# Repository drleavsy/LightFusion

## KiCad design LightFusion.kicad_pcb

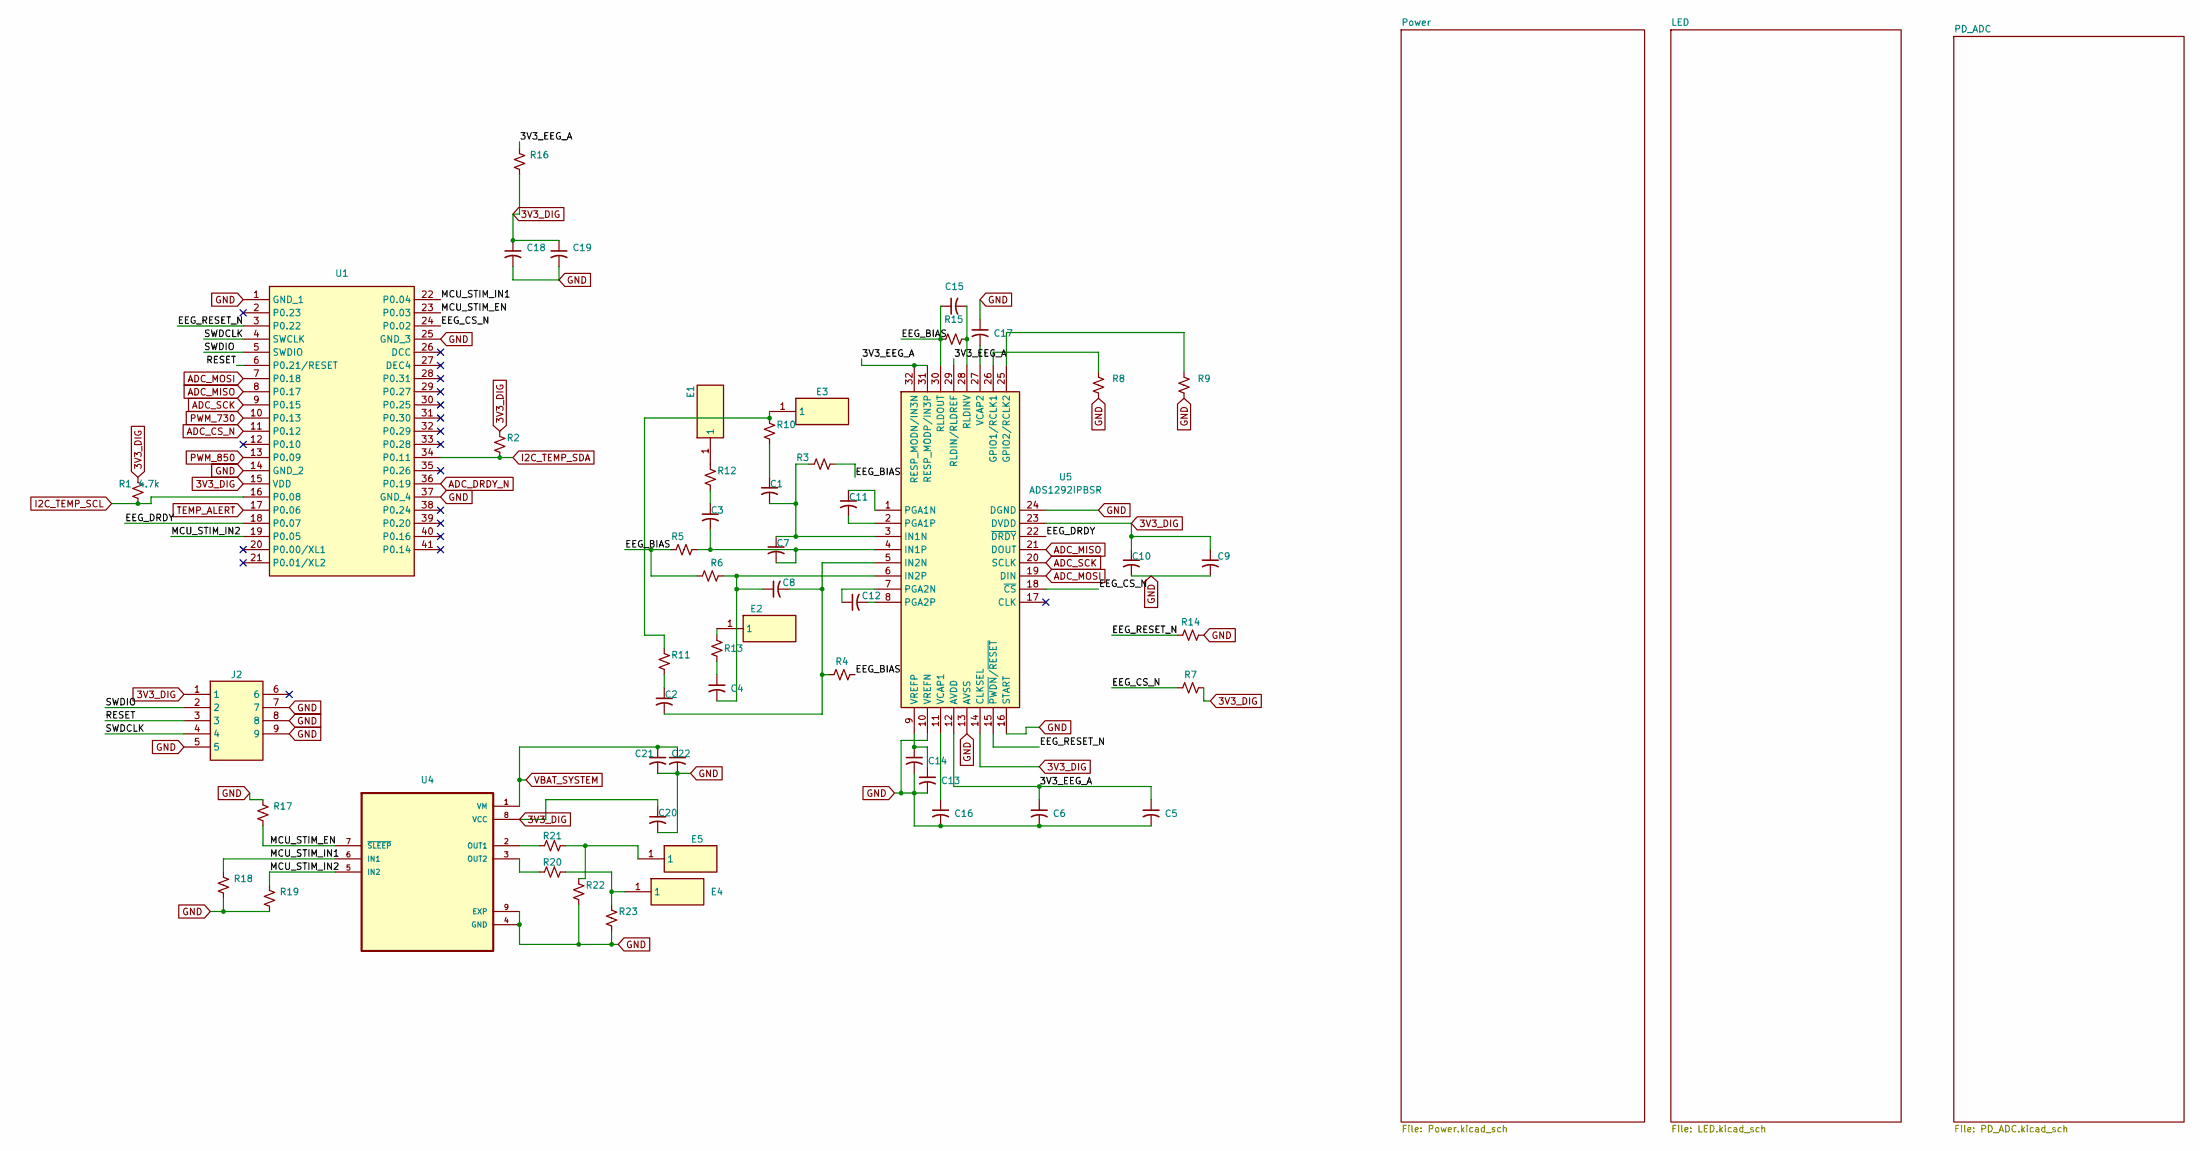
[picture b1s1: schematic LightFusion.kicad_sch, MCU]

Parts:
C1, C2, C3, C4: 47 nF; C_1206_3216Metric
C5, C9, C13: 10 µF; C_0603_1608Metric
C6, C10, C14, C18, C20, C21: 100 nF; C_0603_1608Metric
C7, C8: 2.2 nF; C_0402_1005Metric
C11, C12: 4.7 nF; C_0402_1005Metric
C15: 1.5 nF; C_0402_1005Metric
C16, C17: 1 µF; CAPPC2012X90N
C19: 4.7 uF; C_0603_1608Metric
C22: 1 µF; C_0603_1608Metric
E1, E2, E3, E4, E5: 0914015207714110; Mouser Part Number 575-914015
J2: TC2030-IDC-FP; TC2030IDCFP; Manufacturer_Part_Number TC2030-IDC-NL
R1, R2: 4.7k; R_0603_1608Metric
R3, R4, R5, R6: 22 MΩ; R_0603_1608Metric
R7, R14, R17, R18, R19: 100 kΩ; R_0603_1608Metric
R8, R9: 10 kΩ; R_0603_1608Metric
R10, R11, R12, R13: 51 kΩ; R_0603_1608Metric
R15, R22, R23: 1 MΩ; R_0603_1608Metric
R16: 10 Ω; R_0603_1608Metric
R20, R21: 22 kΩ; R_0603_1608Metric
U1: MDBT42-512KV2; MDBT42512KV2; PARTREV J
U4: DRV8837DSGR
U5: ADS1292IPBSR; Manufacturer_Part_Number ADS1292IPBSR; Mouser Part Number 595-ADS1292IPBSR

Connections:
3V3_DIG: C9.1, C10.1, C18.1, C19.1, C20.1, J2.1, R1.1, R2.1, R7.2, R16.2, U1.15 (VDD), U4.8 (VCC), U5.14 (CLKSEL), U5.23 (DVDD); also elsewhere on the board
/3V3_EEG_A: C5.1, C6.1, R16.1, U5.12 (AVDD), U5.29 (RLDIN/RLDREF), U5.31 (RESP_MODP/IN3P), U5.32 (RESP_MODN/IN3N)
/EEG_BIAS: C15.1, R3.1, R4.2, R5.2, R6.2, R15.1, U5.30 (RLDOUT)
/EEG_CS_N: R7.1, U1.24 (P0.02), U5.18 (~CS)
/EEG_DRDY: U1.18 (P0.07), U5.22 (~DRDY)
/EEG_RESET_N: R14.1, U1.3 (P0.22), U5.15 (~PWDN/~RESET)
/MCU_STIM_EN: R17.2, U1.23 (P0.03), U4.7 (~SLEEP)
/MCU_STIM_IN1: R18.1, U1.22 (P0.04), U4.6 (IN1)
/MCU_STIM_IN2: R19.1, U1.19 (P0.05), U4.5 (IN2)
/RESET: J2.3, U1.6 (P0.21/RESET)
/SWDCLK: J2.4, U1.4 (SWCLK)
/SWDIO: J2.2, U1.5 (SWDIO)
ADC_CS_N: U1.11 (P0.12); also elsewhere on the board
ADC_DRDY_N: U1.36 (P0.19); also elsewhere on the board
ADC_MISO: U1.8 (P0.17), U5.21 (DOUT); also elsewhere on the board
ADC_MOSI: U1.7 (P0.18), U5.19 (DIN); also elsewhere on the board
ADC_SCK: U1.9 (P0.15), U5.20 (SCLK); also elsewhere on the board
GND: C5.2, C6.2, C9.2, C10.2, C13.2, C14.2, C16.2, C17.1, C18.2, C19.2, C20.2, C21.2, C22.2, J2.5, J2.7, J2.8, J2.9, R8.2, R9.2, R14.2, R17.1, R18.2, R19.2, R22.2, R23.2, U1.1 (GND_1), U1.14 (GND_2), U1.25 (GND_3), U1.37 (GND_4), U4.4 (GND), U4.9 (EXP), U5.10 (VREFN), U5.13 (AVSS), U5.16 (START), U5.24 (DGND); also elsewhere on the board
I2C_TEMP_SCL: R1.2, U1.16 (P0.08); also elsewhere on the board
I2C_TEMP_SDA: R2.2, U1.34 (P0.11); also elsewhere on the board
unnamed: C1.1, R10.2
unnamed: C2.1, R11.2
unnamed: C3.1, R12.2
unnamed: C4.1, R13.2
unnamed: E1.1 (1_1), R12.1
unnamed: E2.1 (1_1), R13.1
unnamed: E3.1 (1_1), R10.1, R11.1
unnamed: E4.1 (1_1), R20.2, R23.1
unnamed: E5.1 (1_1), R21.2, R22.1
unnamed: R21.1, U4.2 (OUT1)
unnamed: R20.1, U4.3 (OUT2)
unnamed: R8.1, U5.26 (GPIO1/RCLK1)
unnamed: R9.1, U5.25 (GPIO2/RCLK2)
unnamed: C1.2, C7.1, R3.2, U5.3 (IN1N)
unnamed: C3.2, C7.2, R5.1, U5.4 (IN1P)
unnamed: C2.2, C8.2, R4.1, U5.5 (IN2N)
unnamed: C4.2, C8.1, R6.1, U5.6 (IN2P)
unnamed: C11.1, U5.1 (PGA1N)
unnamed: C11.2, U5.2 (PGA1P)
unnamed: C12.1, U5.7 (PGA2N)
unnamed: C12.2, U5.8 (PGA2P)
unnamed: C15.2, R15.2, U5.28 (RLDINV)
unnamed: C16.1, U5.11 (VCAP1)
unnamed: C17.2, U5.27 (VCAP2)
unnamed: C13.1, C14.1, U5.9 (VREFP)
PWM_730: U1.10 (P0.13); also elsewhere on the board
PWM_850: U1.13 (P0.09); also elsewhere on the board
TEMP_ALERT: U1.17 (P0.06); also elsewhere on the board
VBAT_SYSTEM: C21.1, C22.1, U4.1 (VM); also elsewhere on the board

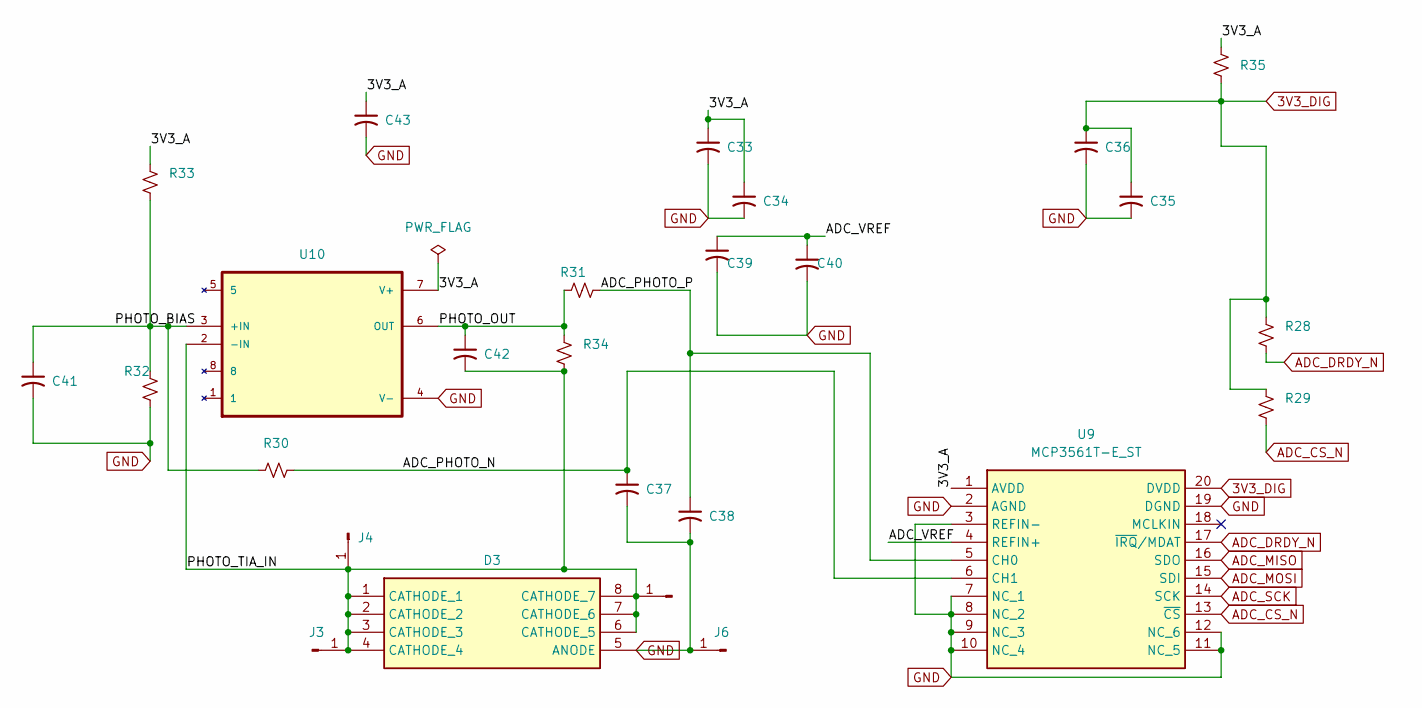
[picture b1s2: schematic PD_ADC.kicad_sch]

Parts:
C33, C34, C36, C40: 100 nF; C_0603_1608Metric
C35: 1uF; C_0603_1608Metric
C37, C38: 100nF; C_1206_3216Metric
C39, C41: 10uF; C_0603_1608Metric
C42: 6.8pF; C_0603_1608Metric
C43: 1 µF; C_0603_1608Metric
D3: VEMD8082; VEMD8082C; Manufacturer_Part_Number VEMD8082; Mouser Part Number 78-VEMD8082
J3, J4, J5, J6: Conn_01x01_Pin; TestPoint_THTPad_1.5x1.5mm_Drill0.7mm
R28, R29, R33, R34: 10k; R_0603_1608Metric
R30, R31: 100R; R_0603_1608Metric
R32: 1.8k; R_0603_1608Metric
R35: 10R; R_0603_1608Metric
U9: MCP3561T-E_ST; Manufacturer_Part_Number MCP3561T-E/ST; Mouser Part Number 579-MCP3561T-E/ST
U10: OPA381AIDGKR

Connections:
3V3_DIG: C35.1, C36.1, R28.1, R29.1, R35.1, U9.20 (DVDD); also elsewhere on the board
/PD_ADC/3V3_A: C33.1, C34.1, C43.1, R33.1, R35.2, U9.1 (AVDD), U10.7 (V+)
/PD_ADC/ADC_PHOTO_N: C37.1, R30.2, U9.6 (CH1)
/PD_ADC/ADC_PHOTO_P: C38.1, R31.2, U9.5 (CH0)
/PD_ADC/ADC_VREF: C39.1, C40.1, U9.4 (REFIN+)
/PD_ADC/PHOTO_BIAS: C41.1, R30.1, R32.1, R33.2, U10.3 (+IN)
/PD_ADC/PHOTO_OUT: C42.1, R31.1, R34.1, U10.6 (OUT)
/PD_ADC/PHOTO_TIA_IN: C42.2, D3.1 (CATHODE_1), D3.2 (CATHODE_2), D3.3 (CATHODE_3), D3.4 (CATHODE_4), D3.6 (CATHODE_5), D3.7 (CATHODE_6), D3.8 (CATHODE_7), J3.1 (Pin_1_1), J4.1 (Pin_1_1), J5.1 (Pin_1_1), R34.2, U10.2 (-IN)
ADC_CS_N: R29.2, U9.13 (~CS); also elsewhere on the board
ADC_DRDY_N: R28.2, U9.17 (~IRQ/MDAT); also elsewhere on the board
ADC_MISO: U9.16 (SDO); also elsewhere on the board
ADC_MOSI: U9.15 (SDI); also elsewhere on the board
ADC_SCK: U9.14 (SCK); also elsewhere on the board
GND: C33.2, C34.2, C35.2, C36.2, C37.2, C38.2, C39.2, C40.2, C41.2, C43.2, D3.5 (ANODE), J6.1 (Pin_1_1), R32.2, U9.2 (AGND), U9.3 (REFIN-), U9.7 (NC_1), U9.8 (NC_2), U9.9 (NC_3), U9.10 (NC_4), U9.11 (NC_5), U9.12 (NC_6), U9.19 (DGND), U10.4 (V-); also elsewhere on the board

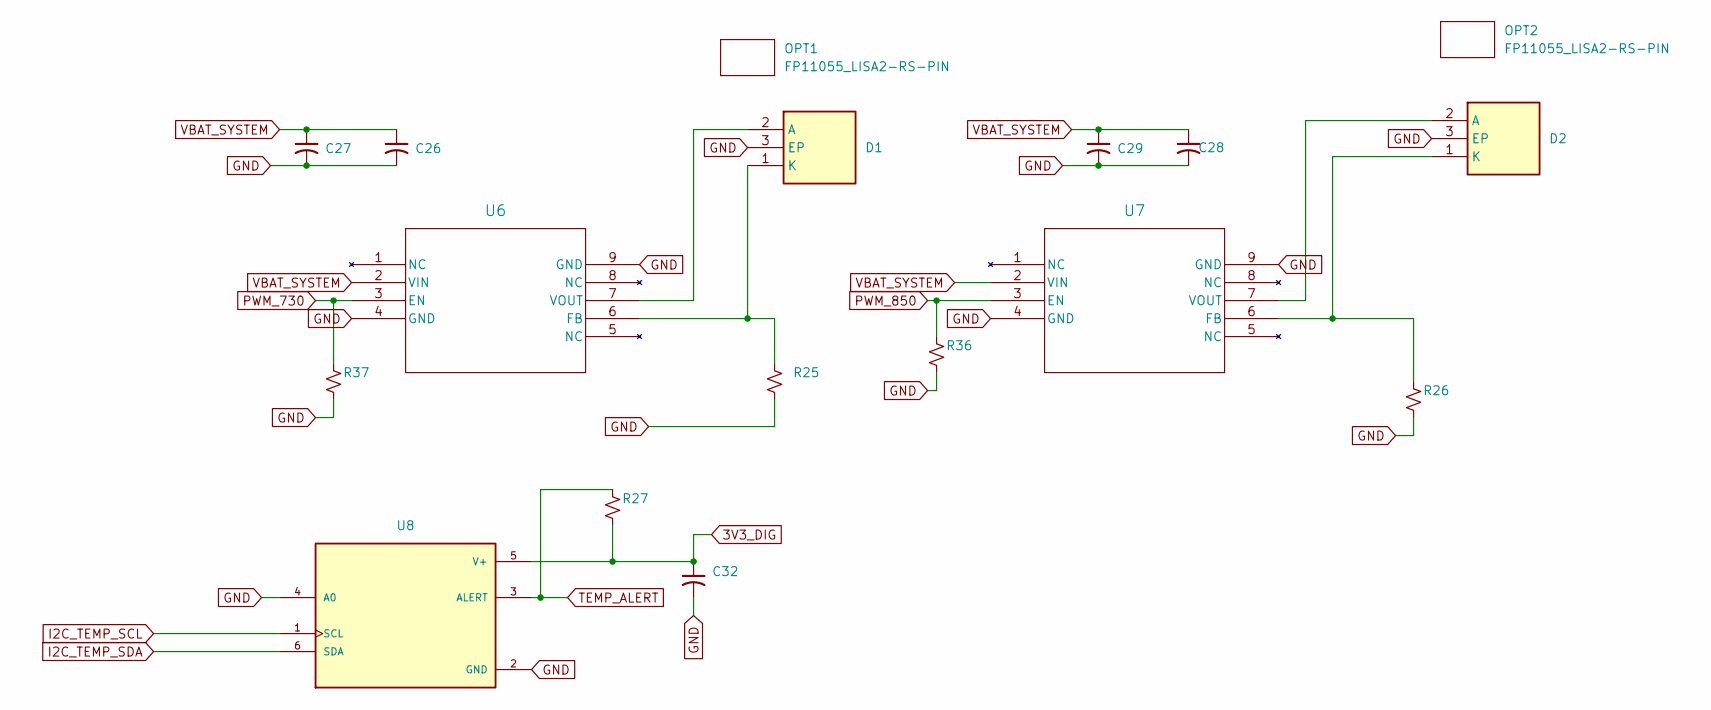
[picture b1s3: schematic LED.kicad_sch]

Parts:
C26, C28: 10 uF; C_0603_1608Metric
C27, C29: 100 nF; C_0603_1608Metric
C32: 10 nF; C_0603_1608Metric
D1, D2: SST-10-IRD-B90H-S810; SST10IRDB90HS810; Manufacturer_Part_Number SST-10-IRD-B90H-S810; Mouser Part Number 896-SST10IRDB90HS81
OPT1, OPT2: FP11055_LISA2-RS-PIN; LEDIL_FP11055_LISA2_RS_PIN
R25, R26: 0.13 Ohm; R_1206_3216Metric
R27: 4.7 kOhm; R_0603_1608Metric
R36, R37: 100k; R_0603_1608Metric
U6, U7: PAM2808BLBR
U8: TMP1075NDRLR; PARTREV E

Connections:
3V3_DIG: C32.1, R27.2, U8.5 (V+); also elsewhere on the board
GND: C26.2, C27.2, C28.2, C29.2, C32.2, D1.3 (EP), D2.3 (EP), R25.2, R26.2, R36.2, R37.2, U6.4 (GND), U6.9 (GND), U7.4 (GND), U7.9 (GND), U8.2 (GND), U8.4 (A0); also elsewhere on the board
I2C_TEMP_SCL: U8.1 (SCL); also elsewhere on the board
I2C_TEMP_SDA: U8.6 (SDA); also elsewhere on the board
unnamed: D1.2 (A), U6.7 (VOUT)
unnamed: D1.1 (K), R25.1, U6.6 (FB)
unnamed: D2.2 (A), U7.7 (VOUT)
unnamed: D2.1 (K), R26.1, U7.6 (FB)
PWM_730: R37.1, U6.3 (EN); also elsewhere on the board
PWM_850: R36.1, U7.3 (EN); also elsewhere on the board
TEMP_ALERT: R27.1, U8.3 (ALERT); also elsewhere on the board
VBAT_SYSTEM: C26.1, C27.1, C28.1, C29.1, U6.2 (VIN), U7.2 (VIN); also elsewhere on the board

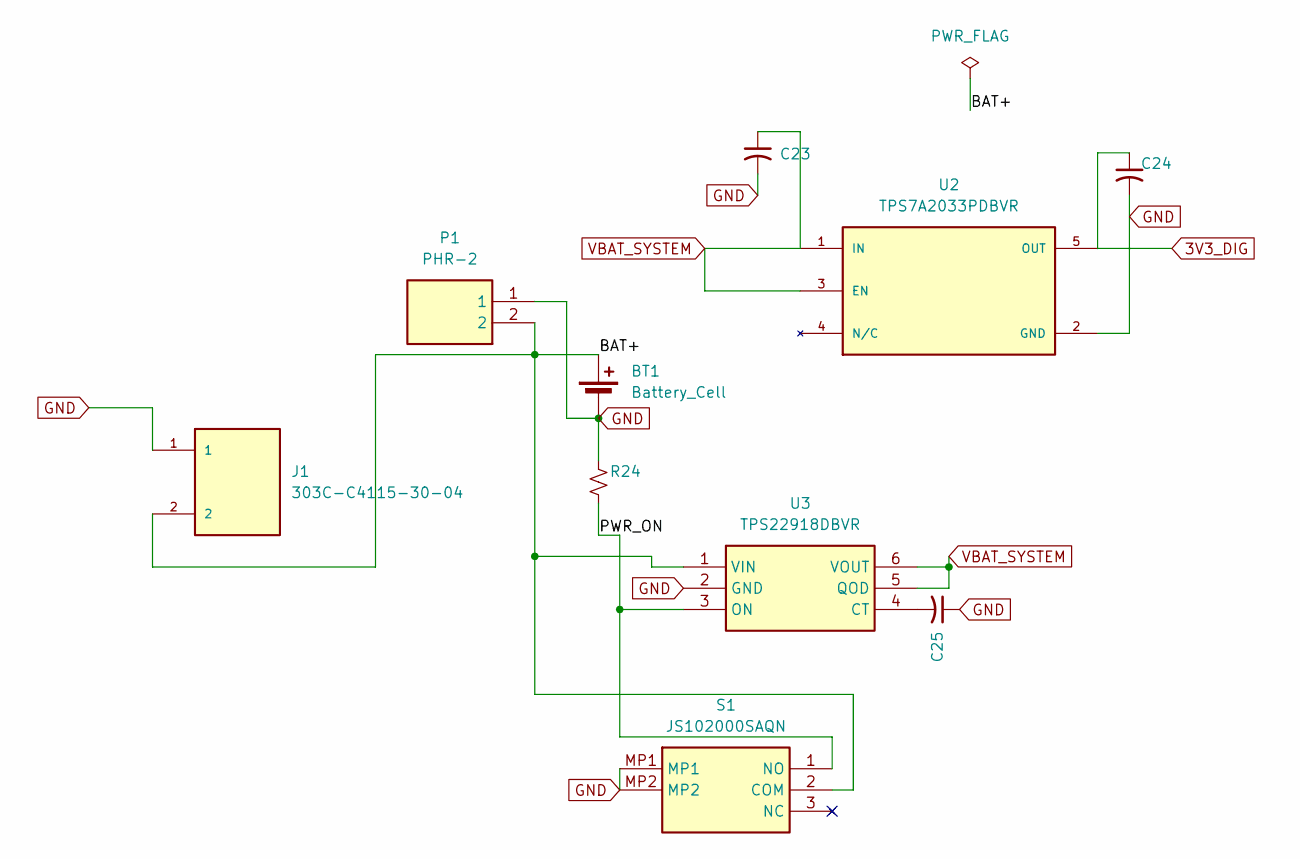
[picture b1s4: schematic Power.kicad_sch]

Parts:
BT1: Battery_Cell
C23, C24: 1 uF; C_0603_1608Metric
C25: 1 nF; C_0603_1608Metric
J1: 303C-C4115-30-04; 303D-L186F020; PARTREV 3
P1: PHR-2; SolderWire-0.5sqmm_1x02_P4.8mm_D0.9mm_OD2.3mm; Manufacturer_Part_Number S2B-PH-K-S
R24: 1 MOhm; R_0603_1608Metric
S1: JS102000SAQN
U2: TPS7A2033PDBVR; PARTREV H
U3: TPS22918DBVR; TPS22918DBVR-6N; Mouser Part Number 595-TPS22918DBVT

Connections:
3V3_DIG: C24.1, U2.5 (OUT); also elsewhere on the board
/Power/BAT+: BT1.1 (+), J1.2, P1.2, S1.2 (COM), U3.1 (VIN)
/Power/PWR_ON: R24.2, S1.1 (NO), U3.3 (ON)
GND: BT1.2 (-), C23.2, C24.2, C25.1, J1.1, P1.1, R24.1, S1.MP1, S1.MP2, U2.2 (GND), U3.2 (GND); also elsewhere on the board
unnamed: C25.2, U3.4 (CT)
VBAT_SYSTEM: C23.1, U2.1 (IN), U2.3 (EN), U3.5 (QOD), U3.6 (VOUT); also elsewhere on the board

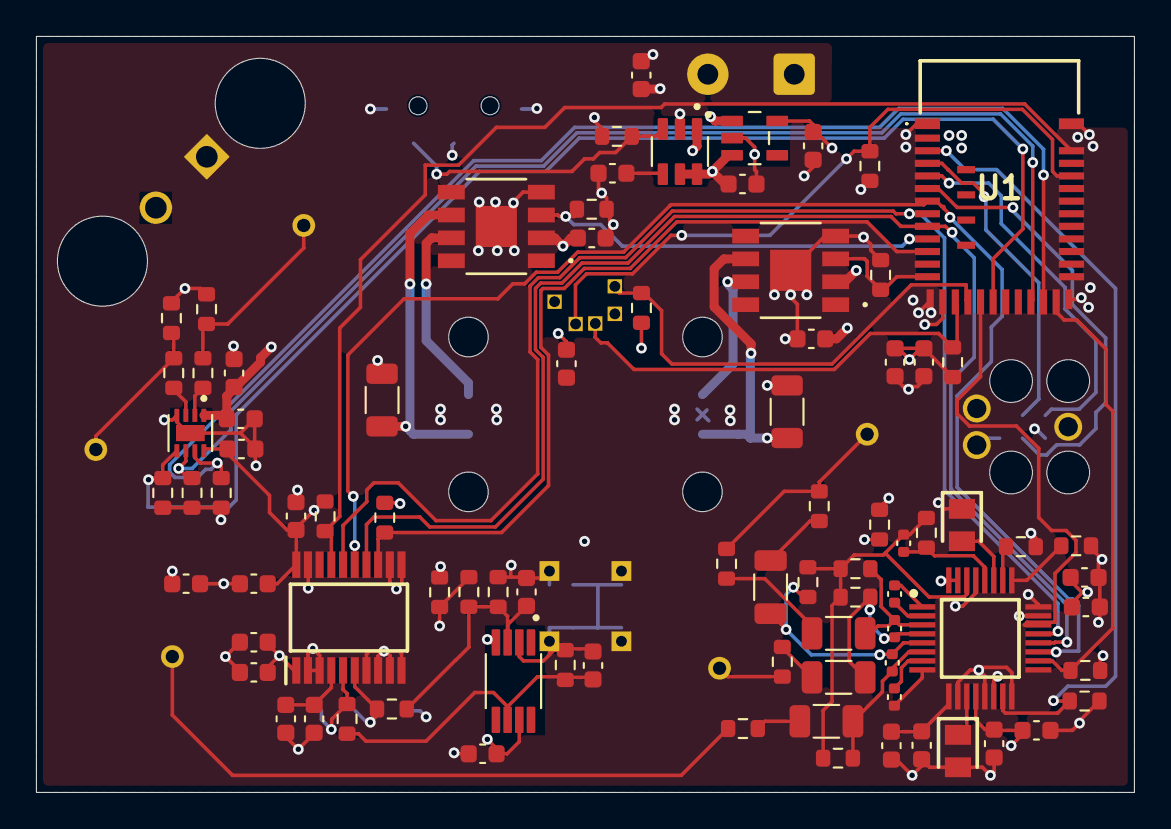
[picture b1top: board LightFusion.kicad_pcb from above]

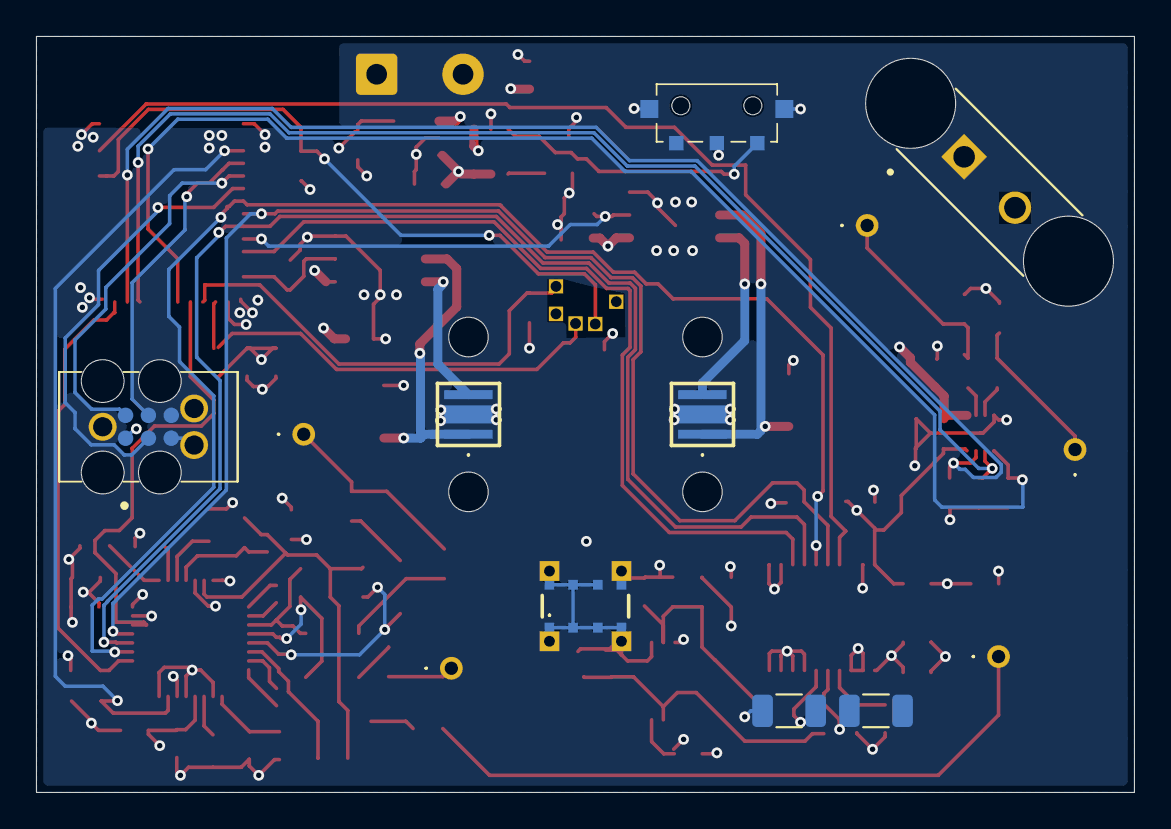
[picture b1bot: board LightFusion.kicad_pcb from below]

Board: 4 copper layers, 61.0 x 42.0 mm, 106 parts (15 on the bottom side), 63 nets.

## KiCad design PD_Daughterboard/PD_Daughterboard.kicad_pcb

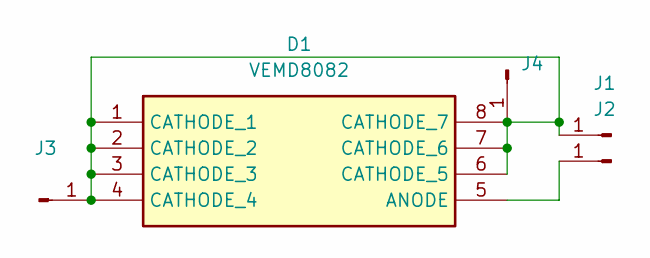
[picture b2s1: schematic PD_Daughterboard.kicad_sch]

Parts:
D1: VEMD8082
J1, J2, J3, J4: Conn_01x01_Pin; TestPoint_THTPad_1.5x1.5mm_Drill0.7mm

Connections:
unnamed: D1.5 (ANODE), J2.1 (Pin_1_1)
unnamed: D1.1 (CATHODE_1), D1.2 (CATHODE_2), D1.3 (CATHODE_3), D1.4 (CATHODE_4), D1.6 (CATHODE_5), D1.7 (CATHODE_6), D1.8 (CATHODE_7), J1.1 (Pin_1_1), J3.1 (Pin_1_1), J4.1 (Pin_1_1)

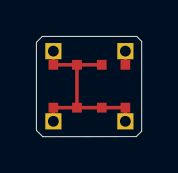
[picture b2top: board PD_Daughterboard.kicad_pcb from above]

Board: 2 copper layers, 5.8 x 5.6 mm, 5 parts (0 on the bottom side), 2 nets.

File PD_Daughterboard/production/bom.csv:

Designator,Footprint,Quantity,Value,LCSC Part #
D1,VEMD8082C,1,VEMD8082,
"J1, J2, J3, J4",TestPoint_THTPad_1.5x1.5mm_Drill0.7mm,4,Conn_01x01_Pin,

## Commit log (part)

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2026-04-30 mcu schematics started
2026-04-30 renamed files
2026-05-01 change of MCU
2026-05-04 mcu ready except antenna
2026-05-04 mcu ready antenna
2026-05-05 footprint
2026-05-06 program socket for MCU footprint
2026-05-07 replace mcu with module due to antenna tuning compexity
2026-05-15 power
2026-05-20 acc_power connector
2026-06-01 error check passed
2026-06-02 placement finished on PCB
2026-06-03 eeg ic was added
2026-06-04 added res, cap, ferrite to eeg part
2026-06-05 eeg part refactored
2026-06-08 eeg part refactored electrodes
2026-06-08 Remove accidental .history submodule
2026-06-08 added pogo electrodes
2026-06-09 eeg 3rd electrode added
2026-06-10 remove silk screen removed from pcb
2026-06-10 2 layers without GND and PWM PWR yet pcb
2026-06-11 4 layers without GND not ready
2026-06-11 refactor GND plane
2026-06-12 3V3 work ongoing in layer 2
2026-06-12 update .gitignore to ignore all history files
2026-06-13 finished power layer 2
2026-06-15 final verifications
2026-06-16 All schematic and pcb checks passed
2026-06-16 Add new electrode positions to positions.csv
    - Added D_730 and D_850 at specified coordinates on the bottom layer.
    - Introduced E_EEG1, E_EEG2, and E_EEG3 at new coordinates on the bottom layer.
    - Included STIM_E_N1 and STIM_E_P1 at new coordinates on the bottom layer.
2026-06-17 changed EEG input filter capacitors from 0603 to 1206 because of availability issue on JLC
2026-06-17 refined electrodes symb
2026-06-17 another electrode symb adjustment
2026-06-18 sync with available parts on JLC
2026-06-22 redesigned MCU part to be able to solder with iron
2026-06-25 final version with bom and placement
